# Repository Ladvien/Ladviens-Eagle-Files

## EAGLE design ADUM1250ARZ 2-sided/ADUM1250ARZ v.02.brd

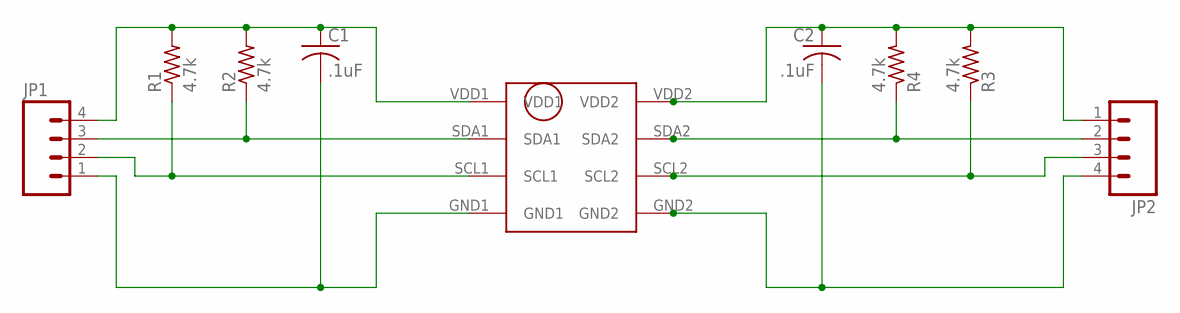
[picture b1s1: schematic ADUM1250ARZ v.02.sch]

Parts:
C1, C2: .1uF; C0402
JP1, JP2: M04PTH; 1X04
R1, R2, R3, R4: 4.7k; R0402
U$1: ADUM1250ARZ

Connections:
GND: C1.2, C2.2, JP1.1, JP2.4, U$1.GND1, U$1.GND2
SCL1: JP1.2, R1.1, U$1.SCL1
SCL2: JP2.3, R3.1, U$1.SCL2
SDA1: JP1.3, R2.1, U$1.SDA1
SDA2: JP2.2, R4.1, U$1.SDA2
VDD1: C1.1, JP1.4, R1.2, R2.2, U$1.VDD1
VDD2: C2.1, JP2.1, R3.2, R4.2, U$1.VDD2

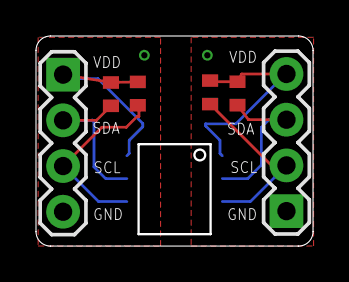
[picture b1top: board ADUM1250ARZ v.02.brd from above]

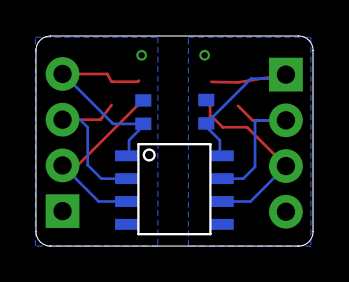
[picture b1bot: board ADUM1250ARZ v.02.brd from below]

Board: 2 copper layers, 15.3 x 11.5 mm, 9 parts (3 on the bottom side), 7 nets.

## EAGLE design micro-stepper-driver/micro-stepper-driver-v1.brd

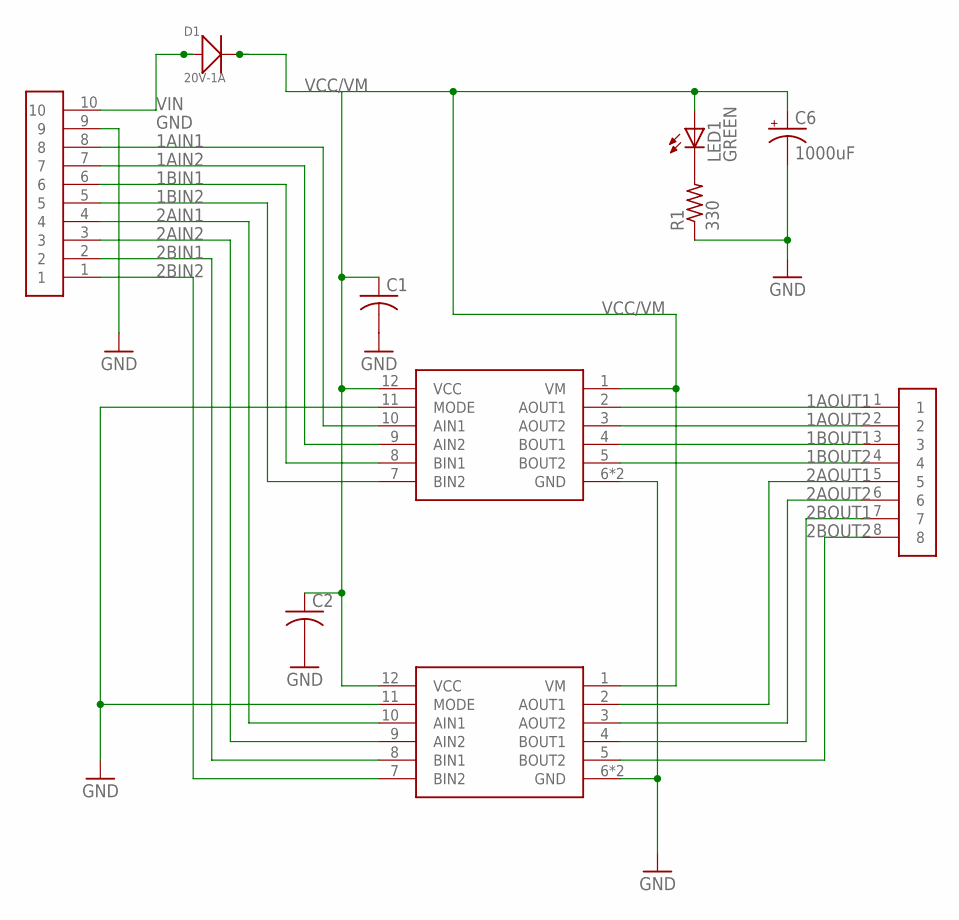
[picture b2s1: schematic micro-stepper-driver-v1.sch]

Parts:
C1, C2: C-USC0402K; C0402K
C6: 1000uF; 153CLV-0810
D1: 20V-1A; SOD-123
LED1: GREEN; SML0603
R1: 330; R0402
U$1, U$4: DRV8835
U$2: EDGE_MOUNT_HEADER_X10; EDGE_MOUNT_HEAD_X10
U$3: EDGE_MOUNT_HEAD_X8

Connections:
1AIN1: U$2.8, U$4.10 (AIN1)
1AIN2: U$2.7, U$4.9 (AIN2)
1AOUT1: U$3.1, U$4.2 (AOUT1)
1AOUT2: U$3.2, U$4.3 (AOUT2)
1BIN1: U$2.6, U$4.8 (BIN1)
1BIN2: U$2.5, U$4.7 (BIN2)
1BOUT1: U$3.3, U$4.4 (BOUT1)
1BOUT2: U$3.4, U$4.5 (BOUT2)
2AIN1: U$1.10 (AIN1), U$2.4
2AIN2: U$1.9 (AIN2), U$2.3
2AOUT1: U$1.2 (AOUT1), U$3.5
2AOUT2: U$1.3 (AOUT2), U$3.6
2BIN1: U$1.8 (BIN1), U$2.2
2BIN2: U$1.7 (BIN2), U$2.1
2BOUT1: U$1.4 (BOUT1), U$3.7
2BOUT2: U$1.5 (BOUT2), U$3.8
GND: C1.2, C2.2, C6.-, R1.1, U$1.6 (GND), U$1.11 (MODE), U$1.PAD (GND), U$2.9, U$4.6 (GND), U$4.11 (MODE), U$4.PAD (GND)
unnamed: LED1.C, R1.2
VCC/VM: C1.1, C2.1, C6.+, D1.-, LED1.A, U$1.1 (VM), U$1.12 (VCC), U$4.1 (VM), U$4.12 (VCC)
VIN: D1.+, U$2.10

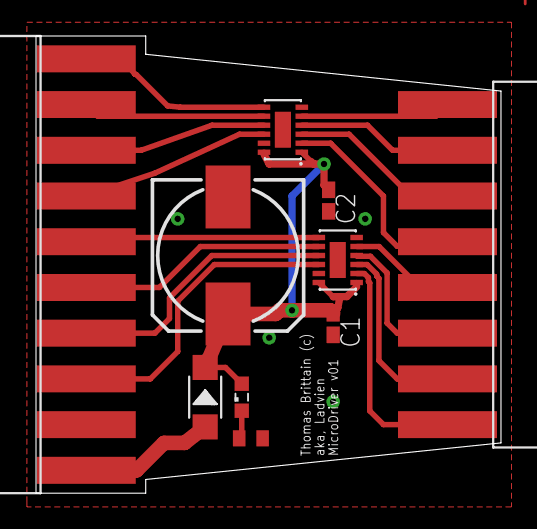
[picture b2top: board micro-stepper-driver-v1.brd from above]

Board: 2 copper layers, 25.8 x 25.4 mm, 10 parts (0 on the bottom side), 20 nets.

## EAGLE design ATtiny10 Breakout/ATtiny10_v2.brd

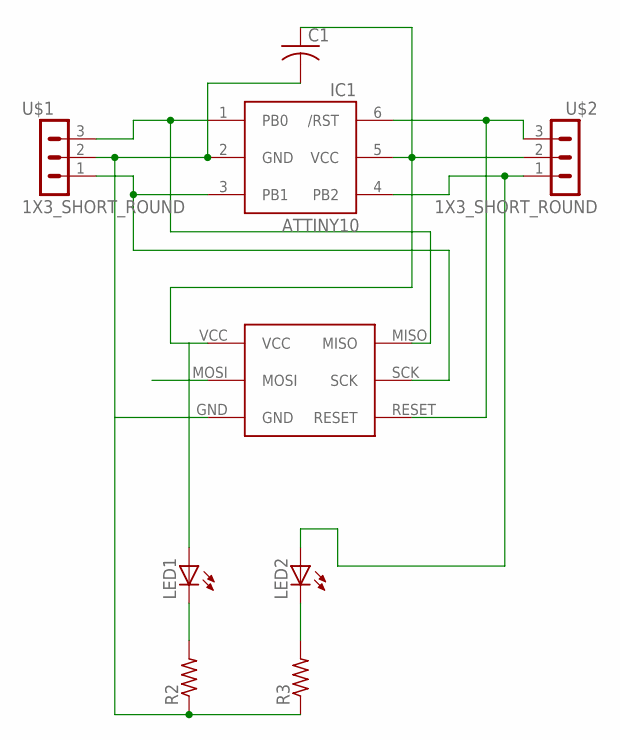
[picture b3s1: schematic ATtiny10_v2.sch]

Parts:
C1: C-USC0402K; C0402K
IC1: ATTINY10; SOT23-6
LED1, LED2: LEDCHIPLED_0603; CHIPLED_0603
R2, R3: R-US_R0402; R0402
U$1, U$2: 1X3_SHORT_ROUND
U$4: TINY-AVR-POGO-PIN-KEY

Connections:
GND: C1.2, IC1.2 (GND), R2.1, R3.1, U$1.2 (5), U$4.GND
unnamed: LED1.C, R2.2
unnamed: LED2.C, R3.2
PB0: IC1.1 (PB0), U$1.3 (6), U$4.MISO
PB1: IC1.3 (PB1), U$1.1 (4), U$4.SCK
PB2: IC1.4 (PB2), LED2.A, U$2.1 (4)
RST: IC1.6 (/RST), U$2.3 (6), U$4.RESET
VCC: C1.1, IC1.5 (VCC), LED1.A, U$2.2 (5), U$4.VCC

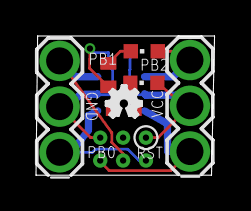
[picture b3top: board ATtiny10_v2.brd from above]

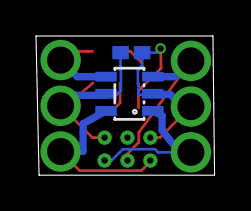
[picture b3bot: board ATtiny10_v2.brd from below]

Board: 2 copper layers, 9.9 x 7.7 mm, 10 parts (2 on the bottom side), 8 nets.

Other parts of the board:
U$3: OSHW_FILLX70_NOTEXT

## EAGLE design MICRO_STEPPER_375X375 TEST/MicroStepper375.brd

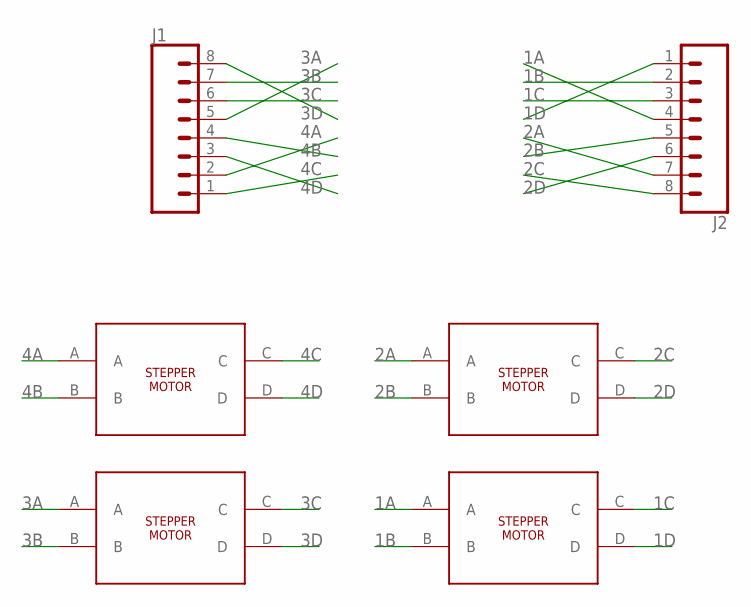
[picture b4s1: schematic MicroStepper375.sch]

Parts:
J1, J2: CONN_08NO_SILK_FEMALE_PTH; 1X08_NO_SILK
U$1, U$2, U$3, U$4: MICRO_STEPPER_375X375

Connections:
1A: J2.4, U$4.A
1B: J2.2, U$4.B
1C: J2.3, U$4.C
1D: J2.1, U$4.D
2A: J2.7, U$3.A
2B: J2.5, U$3.B
2C: J2.8, U$3.C
2D: J2.6, U$3.D
3A: J1.5, U$2.A
3B: J1.7, U$2.B
3C: J1.6, U$2.C
3D: J1.8, U$2.D
4A: J1.2, U$1.A
4B: J1.4, U$1.B
4C: J1.1, U$1.C
4D: J1.3, U$1.D

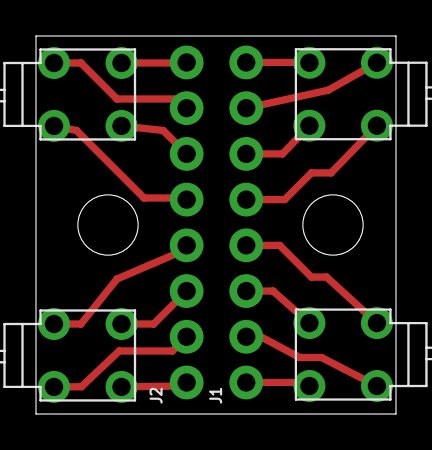
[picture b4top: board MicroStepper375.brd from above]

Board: 2 copper layers, 20.0 x 21.0 mm, 6 parts (0 on the bottom side), 16 nets.

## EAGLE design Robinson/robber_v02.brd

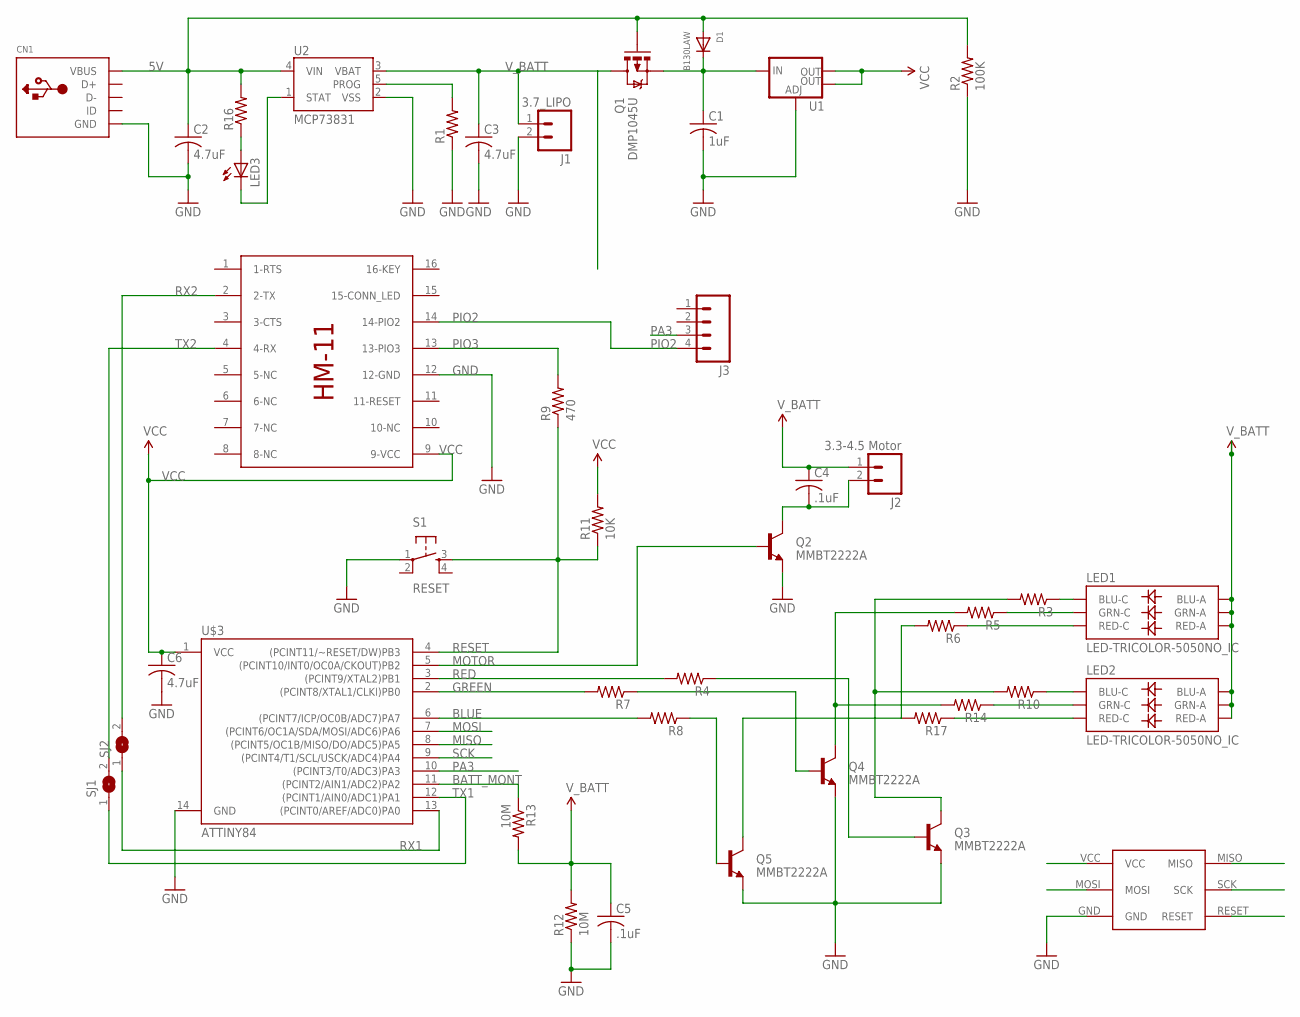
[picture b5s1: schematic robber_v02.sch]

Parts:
C1: 1uF; C0805K
C2: 4.7uF; C0805K
C3, C6: 4.7uF; C0805
C4: .1uF; C0402K
C5: .1uF; C0805
CN1: USBMINIB; USB-MINIB
D1: B130LAW; SOD-123
J1: 3.7_LIPO; 1X02
J2: 3.3-4.5 Motor; 1X02
J3: M04PTH; 1X04
LED1, LED2: LED-TRICOLOR-5050NO_IC; LED-TRICOLOR-5050
LED3: LEDSML0603; SML0603
Q1: DMP1045U; SOT23-3
Q2, Q3, Q4, Q5: MMBT2222A; SOT23-3
R1, R16: R-US_R0805W; R0805W
R2: 100K; R0805W
R3, R4, R5, R6, R7, R8, R10, R14, R17: R-US_R0402; R0402
R9: 470; R0805
R11: 10K; R0805W
R12, R13: 10M; R0805W
S1: RESET; TACTILE-SWITCH-SMD
SJ1, SJ2: SJ
U1: V_REG_LM1117SOT223; SOT223
U2: MCP73831; SOT23-5
U$1: HM-11
U$3: ATTINY84; SO14
U$5: TINY-AVR-POGO-PIN-KEY

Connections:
5V: C2.1, CN1.VBUS, D1.A, Q1.1 (G), R2.2, R16.2, U2.4 (VIN)
BATT_MONT: R13.1, U$3.11 ((PCINT2/AIN1/ADC2)PA2)
BLUE: R8.2, U$3.6 ((PCINT7/ICP/OC0B/ADC7)PA7)
GND: C1.2, C2.2, C3.2, C5.2, C6.2, CN1.GND, CN1.GND1 (GND), CN1.GND2 (GND), CN1.GND3 (GND), CN1.GND4 (GND), J1.2, Q2.2 (E), Q3.2 (E), Q4.2 (E), Q5.2 (E), R1.1, R2.1, R12.1, S1.1, U1.1 (ADJ), U2.2 (VSS), U$1.12 (12-GND), U$3.14 (GND), U$5.GND
GREEN: R7.2, U$3.2 ((PCINT8/XTAL1/CLKI)PB0)
MISO: U$3.8 ((PCINT5/OC1B/MISO/DO/ADC5)PA5), U$5.MISO
MOSI: U$3.7 ((PCINT6/OC1A/SDA/MOSI/ADC6)PA6), U$5.MOSI
MOTOR: Q2.1 (B), U$3.5 ((PCINT10/INT0/OC0A/CKOUT)PB2)
unnamed: LED3.A, R16.1
unnamed: LED3.C, U2.1 (STAT)
unnamed: C1.1, D1.C, Q1.2 (S), U1.3 (IN)
unnamed: LED1.4 (BLU-C), R3.1
unnamed: LED1.6 (GRN-C), R5.1
unnamed: C4.2, J2.2, Q2.3 (C)
unnamed: LED1.5 (RED-C), R6.1
unnamed: LED2.4 (BLU-C), R10.1
unnamed: LED2.6 (GRN-C), R14.1
unnamed: LED2.5 (RED-C), R17.1
unnamed: Q3.3 (C), R3.2, R10.2
unnamed: Q3.1 (B), R4.1
unnamed: Q4.3 (C), R5.2, R14.2
unnamed: Q4.1 (B), R7.1
unnamed: Q5.1 (B), R8.1
unnamed: Q5.3 (C), R6.2, R17.2
unnamed: R1.2, U2.5 (PROG)
PA3: J3.3, U$3.10 ((PCINT3/T0/ADC3)PA3)
PIO2: J3.4, U$1.14 (14-PIO2)
PIO3: R9.2, U$1.13 (13-PIO3)
RED: R4.2, U$3.3 ((PCINT9/XTAL2)PB1)
RESET: R9.1, R11.1, S1.3, U$3.4 ((PCINT11/~RESET/DW)PB3), U$5.RESET
RX1: SJ2.1, U$3.13 ((PCINT0/AREF/ADC0)PA0)
RX2: SJ2.2, U$1.2 (2-TX)
SCK: U$3.9 ((PCINT4/T1/SCL/USCK/ADC4)PA4), U$5.SCK
TX1: SJ1.1, U$3.12 ((PCINT1/AIN0/ADC1)PA1)
TX2: SJ1.2, U$1.4 (4-RX)
VCC: C6.1, R11.2, U1.2 (OUT), U1.4 (OUT), U$1.9 (9-VCC), U$3.1 (VCC), U$5.VCC
V_BATT: C3.1, C4.1, C5.1, J1.1, J2.1, LED1.1 (GRN-A), LED1.2 (RED-A), LED1.3 (BLU-A), LED2.1 (GRN-A), LED2.2 (RED-A), LED2.3 (BLU-A), Q1.3 (D), R12.2, R13.2, U2.3 (VBAT)

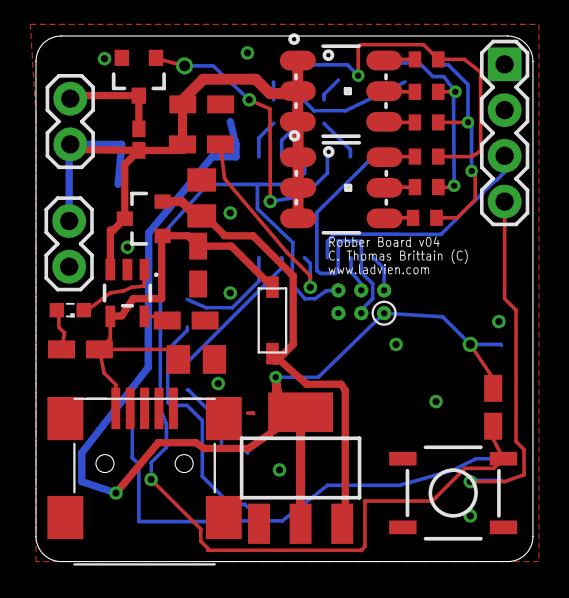
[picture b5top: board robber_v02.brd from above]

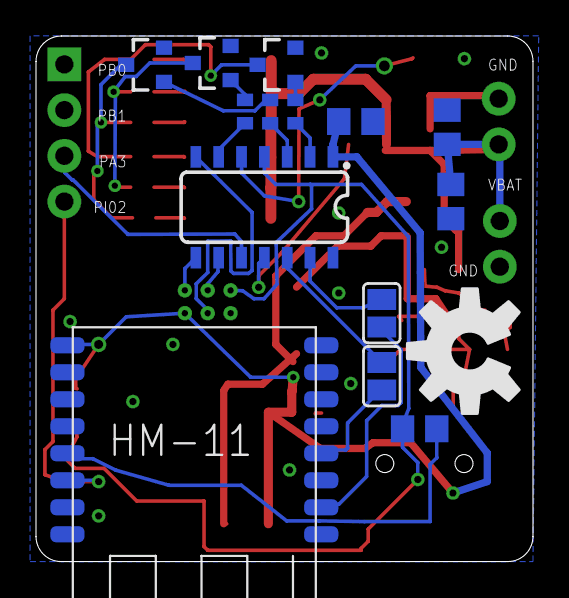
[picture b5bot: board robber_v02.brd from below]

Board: 2 copper layers, 27.6 x 29.2 mm, 44 parts (15 on the bottom side), 37 nets.

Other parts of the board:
U$2: OSHW-LOGO-L

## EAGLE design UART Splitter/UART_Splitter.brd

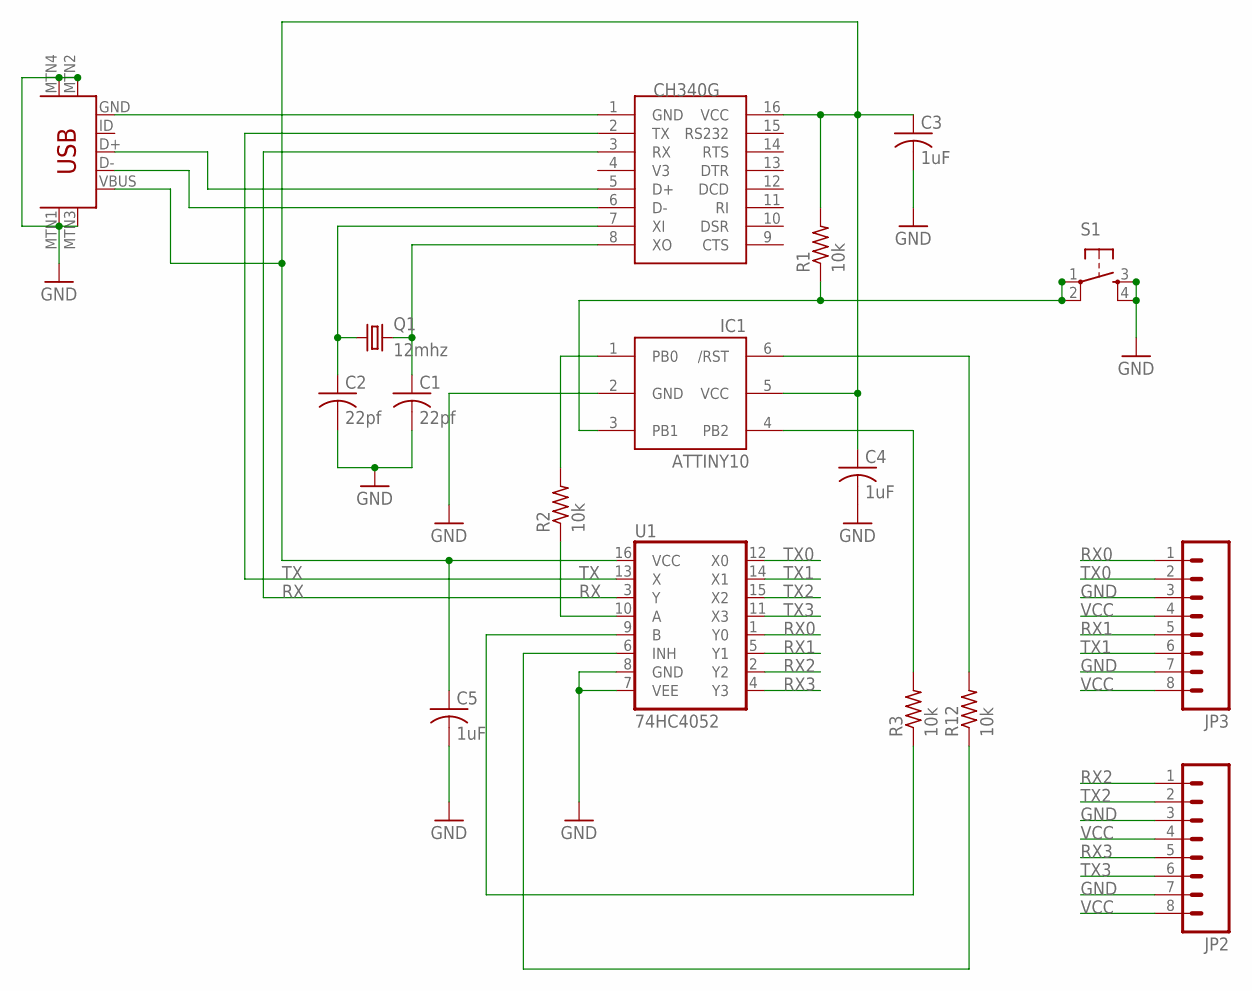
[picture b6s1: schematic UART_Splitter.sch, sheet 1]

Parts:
C1, C2: 22pf; C0402K
C3, C4, C5: 1uF; C0402K
IC1: ATTINY10; SOT23-6
JP2, JP3: M081X08; 1X08
Q1: 12mhz; HC49UP
R1, R2, R3, R12: 10k; R0402
S1: TAC_SWITCHSMD; TACTILE_SWITCH_SMD
U1: 74HC4052; SO16
U$1: CH340G; SOIC16
U$2: USB-MINIB-5PIN; USB-MINIB

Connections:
GND: C1.2, C2.2, C3.2, C4.2, C5.2, IC1.2 (GND), JP2.3, JP2.7, JP3.3, JP3.7, S1.3, S1.4, U1.7 (VEE), U1.8 (GND), U$1.1 (GND), U$2.GND, U$2.MTN1 (MTN2), U$2.MTN2 (MTN3), U$2.MTN3 (MTN1), U$2.MTN4
unnamed: U$1.5 (D+), U$2.D+
unnamed: U$1.6 (D-), U$2.D-
unnamed: R2.1, U1.10 (A)
unnamed: R3.1, U1.9 (B)
unnamed: IC1.3 (PB1), R1.1, S1.1, S1.2
unnamed: IC1.6 (/RST), R12.2
unnamed: IC1.1 (PB0), R2.2
unnamed: C2.1, Q1.1, U$1.7 (XI)
unnamed: C1.1, Q1.2, U$1.8 (XO)
unnamed: IC1.4 (PB2), R3.2
unnamed: R12.1, U1.6 (INH)
RX: U1.3 (Y), U$1.3 (RX)
RX0: JP3.1, U1.1 (Y0); also elsewhere on the board
RX1: JP3.5, U1.5 (Y1); also elsewhere on the board
RX2: JP2.1, U1.2 (Y2); also elsewhere on the board
RX3: JP2.5, U1.4 (Y3); also elsewhere on the board
TX: U1.13 (X), U$1.2 (TX)
TX0: JP3.2, U1.12 (X0); also elsewhere on the board
TX1: JP3.6, U1.14 (X1); also elsewhere on the board
TX2: JP2.2, U1.15 (X2); also elsewhere on the board
TX3: JP2.6, U1.11 (X3); also elsewhere on the board
VCC: C3.1, C4.1, C5.1, IC1.5 (VCC), JP2.4, JP2.8, JP3.4, JP3.8, R1.2, U1.16 (VCC), U$1.16 (VCC), U$2.VBUS; also elsewhere on the board

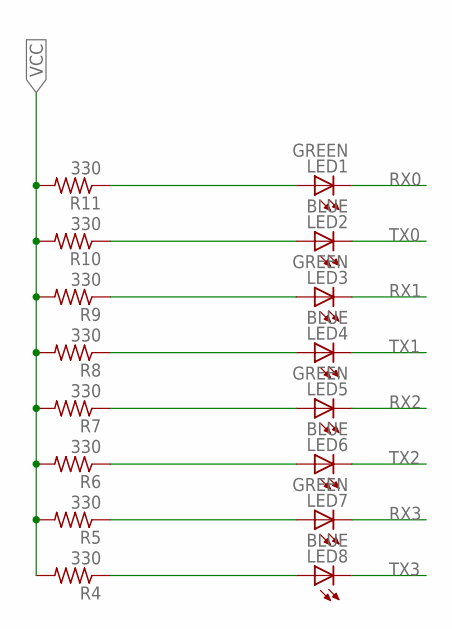
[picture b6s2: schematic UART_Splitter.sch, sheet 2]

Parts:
LED1, LED3, LED5, LED7: GREEN; SML0603
LED2, LED4, LED6, LED8: BLUE; SML0603
R4, R5, R6, R7, R8, R9, R10, R11: 330; R0402

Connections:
LED_RX0: LED1.A, R11.1
LED_RX1: LED3.A, R9.1
LED_RX2: LED5.A, R7.1
LED_RX3: LED7.A, R5.1
LED_TX0: LED2.A, R10.1
LED_TX1: LED4.A, R8.1
LED_TX2: LED6.A, R6.1
LED_TX3: LED8.A, R4.1
RX0: LED1.C; also elsewhere on the board
RX1: LED3.C; also elsewhere on the board
RX2: LED5.C; also elsewhere on the board
RX3: LED7.C; also elsewhere on the board
TX0: LED2.C; also elsewhere on the board
TX1: LED4.C; also elsewhere on the board
TX2: LED6.C; also elsewhere on the board
TX3: LED8.C; also elsewhere on the board
VCC: R4.2, R5.2, R6.2, R7.2, R8.2, R9.2, R10.2, R11.2; also elsewhere on the board

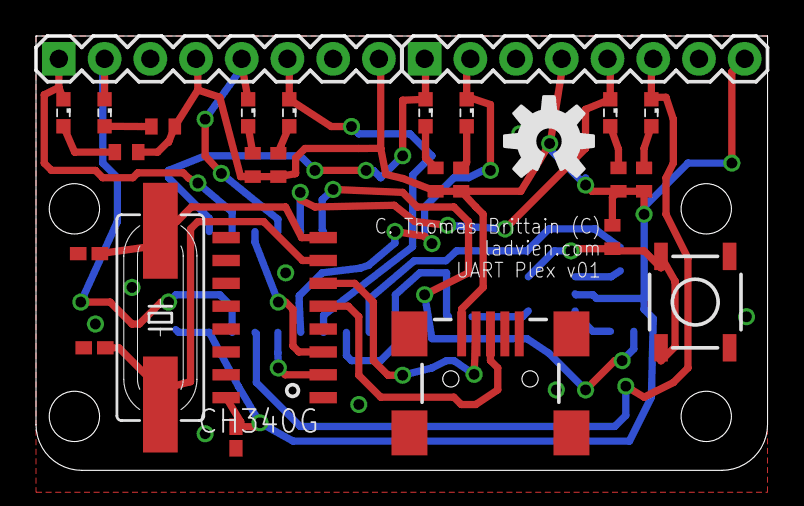
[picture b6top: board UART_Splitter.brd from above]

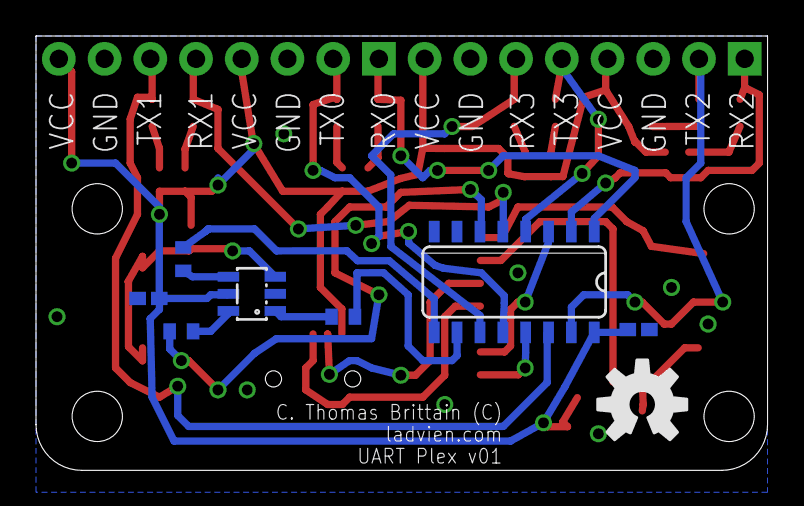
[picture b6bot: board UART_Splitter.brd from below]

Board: 2 copper layers, 40.6 x 24.1 mm, 35 parts (8 on the bottom side), 31 nets.

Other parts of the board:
U$3, U$4: OSHW-LOGO-M

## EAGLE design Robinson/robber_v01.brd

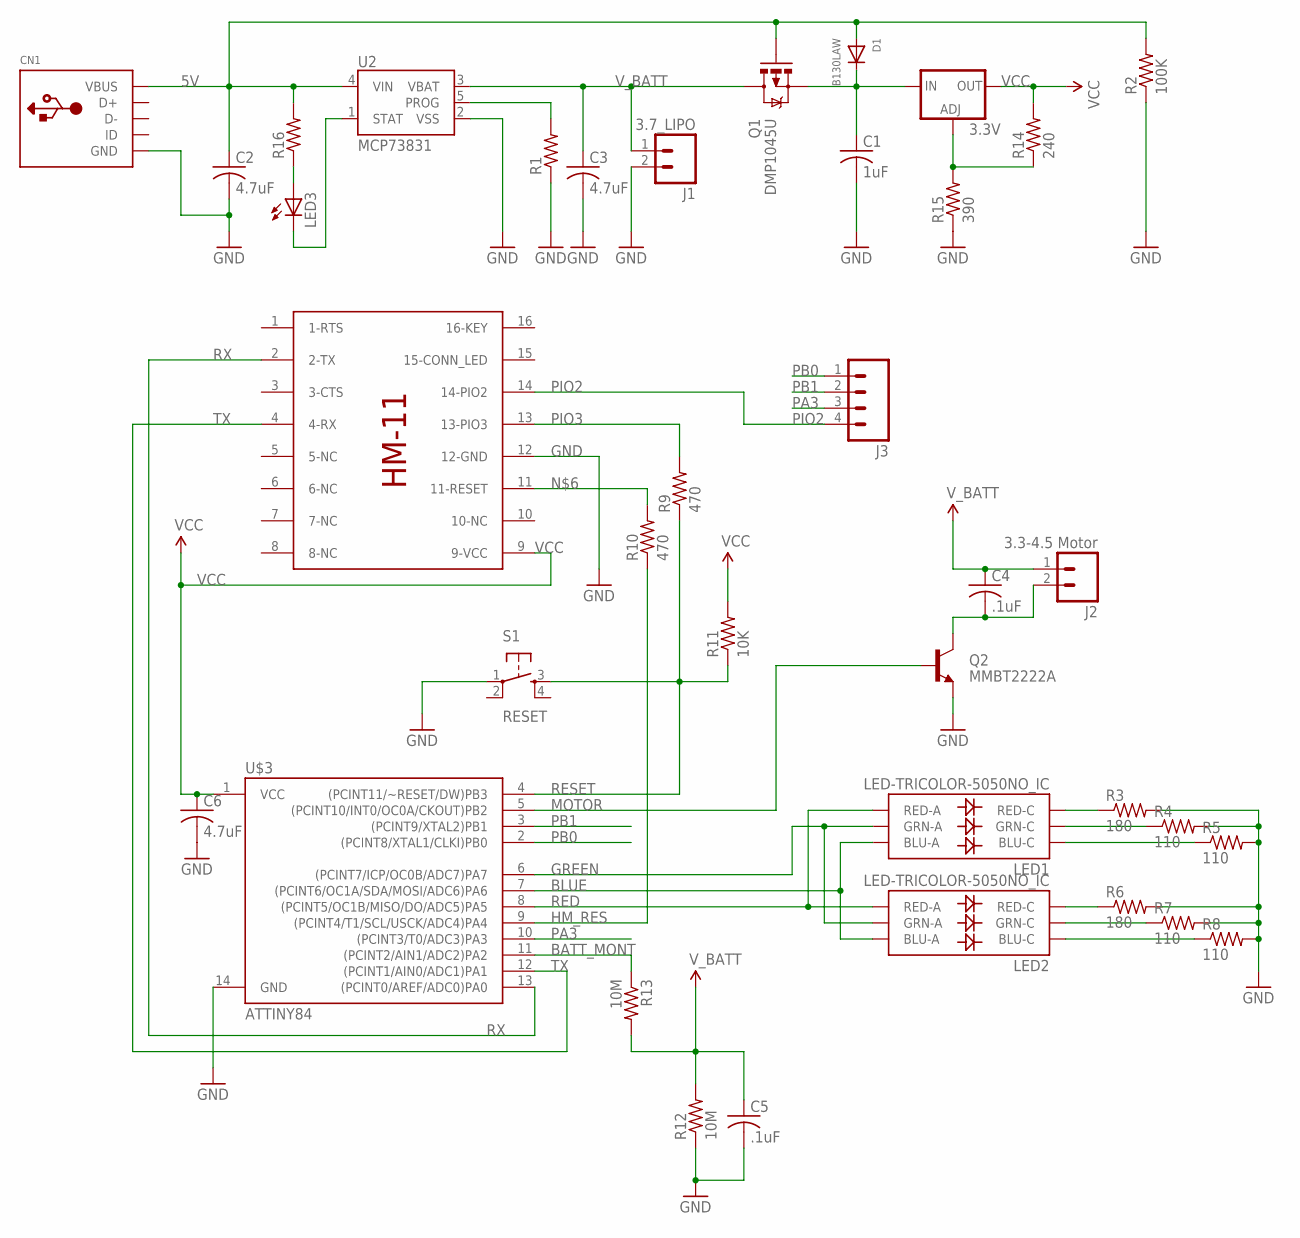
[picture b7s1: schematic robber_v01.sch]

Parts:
3.3V: V_REG_317SMD; SOT223
C1: 1uF; C0805
C2, C3, C6: 4.7uF; C0805
C4, C5: .1uF; C0805
CN1: USBMINIB; USB-MINIB
D1: B130LAW; SOD-123
J1: 3.7_LIPO; 1X02
J2: 3.3-4.5 Motor; 1X02
J3: M04PTH; 1X04
LED1, LED2: LED-TRICOLOR-5050NO_IC; LED-TRICOLOR-5050
LED3: LEDSML0603; SML0603
Q1: DMP1045U; SOT23-3
Q2: MMBT2222A; SOT23-3
R1, R16: R-US_R0805; R0805
R2: 100K; R0805
R3, R6: 180; R0805
R4, R5, R7, R8: 110; R0805
R9, R10: 470; R0805
R11: 10K; R0805
R12, R13: 10M; R0805
R14: 240; R0805
R15: 390; R0805
S1: RESET; TACTILE-SWITCH-SMD
U2: MCP73831; SOT23-5
U$1: HM-11
U$3: ATTINY84; SO14

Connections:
5V: C2.1, CN1.VBUS, D1.A, Q1.1 (G), R2.2, R16.2, U2.4 (VIN)
BATT_MONT: R13.1, U$3.11 ((PCINT2/AIN1/ADC2)PA2)
BLUE: LED1.3 (BLU-A), LED2.3 (BLU-A), U$3.7 ((PCINT6/OC1A/SDA/MOSI/ADC6)PA6)
GND: C1.2, C2.2, C3.2, C5.2, C6.2, CN1.GND, CN1.GND1 (GND), CN1.GND2 (GND), CN1.GND3 (GND), CN1.GND4 (GND), J1.2, Q2.2 (E), R1.1, R2.1, R3.2, R4.2, R5.2, R6.2, R7.2, R8.2, R12.1, R15.1, S1.1, U2.2 (VSS), U$1.12 (12-GND), U$3.14 (GND)
GREEN: LED1.1 (GRN-A), LED2.1 (GRN-A), U$3.6 ((PCINT7/ICP/OC0B/ADC7)PA7)
HM_RES: R10.1, U$3.9 ((PCINT4/T1/SCL/USCK/ADC4)PA4)
MOTOR: Q2.1 (B), U$3.5 ((PCINT10/INT0/OC0A/CKOUT)PB2)
unnamed: LED3.A, R16.1
unnamed: LED3.C, U2.1 (STAT)
unnamed: R10.2, U$1.11 (11-RESET)
unnamed: C4.2, J2.2, Q2.3 (C)
unnamed: 3.3V.1 (ADJ), R14.1, R15.2
unnamed: LED1.5 (RED-C), R3.1
unnamed: 3.3V.3 (IN), C1.1, D1.C, Q1.2 (S)
unnamed: R1.2, U2.5 (PROG)
unnamed: LED1.6 (GRN-C), R4.1
unnamed: LED1.4 (BLU-C), R5.1
unnamed: LED2.5 (RED-C), R6.1
unnamed: LED2.6 (GRN-C), R7.1
unnamed: LED2.4 (BLU-C), R8.1
PA3: J3.3, U$3.10 ((PCINT3/T0/ADC3)PA3)
PB0: J3.1, U$3.2 ((PCINT8/XTAL1/CLKI)PB0)
PB1: J3.2, U$3.3 ((PCINT9/XTAL2)PB1)
PIO2: J3.4, U$1.14 (14-PIO2)
PIO3: R9.2, U$1.13 (13-PIO3)
RED: LED1.2 (RED-A), LED2.2 (RED-A), U$3.8 ((PCINT5/OC1B/MISO/DO/ADC5)PA5)
RESET: R9.1, R11.1, S1.3, U$3.4 ((PCINT11/~RESET/DW)PB3)
RX: U$1.2 (2-TX), U$3.13 ((PCINT0/AREF/ADC0)PA0)
TX: U$1.4 (4-RX), U$3.12 ((PCINT1/AIN0/ADC1)PA1)
VCC: 3.3V.2 (OUT), C6.1, R11.2, R14.2, U$1.9 (9-VCC), U$3.1 (VCC)
V_BATT: C3.1, C4.1, C5.1, J1.1, J2.1, Q1.3 (D), R12.2, R13.2, U2.3 (VBAT)

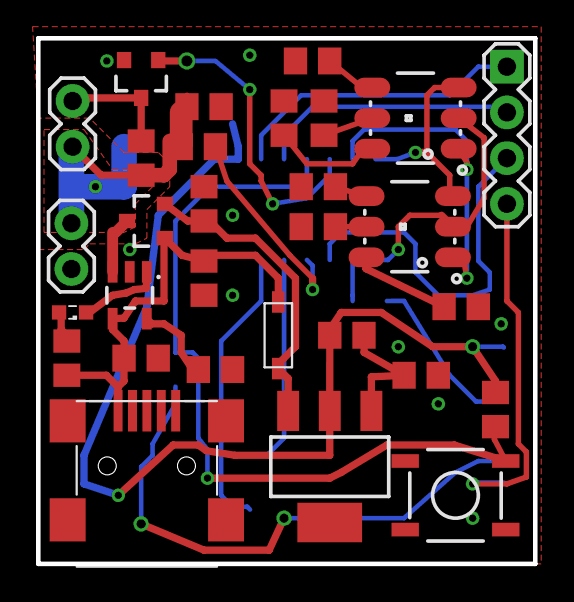
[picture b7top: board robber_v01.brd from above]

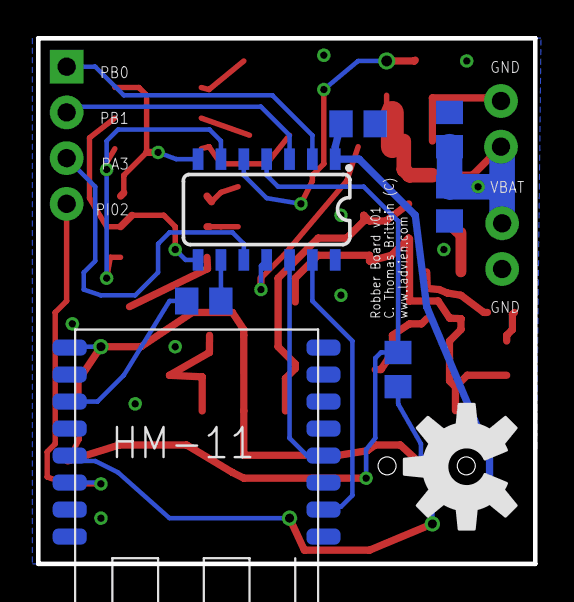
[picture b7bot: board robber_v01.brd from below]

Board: 2 copper layers, 27.6 x 29.2 mm, 38 parts (8 on the bottom side), 31 nets.

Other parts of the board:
U$2: OSHW-LOGO-L

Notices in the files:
parts and their libraries:
SparkFun: Licensing: CC v3.0 Share-Alike You are welcome to use this library for commercial purposes.
SparkFun-Connectors: Licensing: Creative Commons ShareAlike 4.0 International - https://creativecommons.org/licenses/by-sa/4.0
